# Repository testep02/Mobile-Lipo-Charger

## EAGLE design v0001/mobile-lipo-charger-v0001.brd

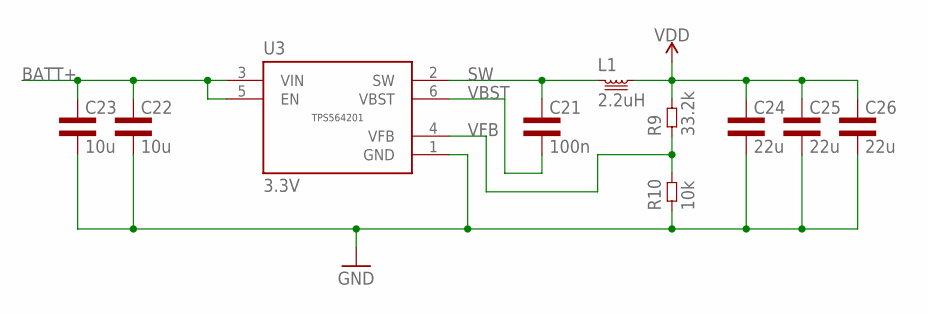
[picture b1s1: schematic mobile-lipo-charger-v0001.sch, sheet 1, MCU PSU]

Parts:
C21: 100n; 0603L3
C22, C23: 10u; 1206L3
C24, C25, C26: 22u; 0603L3
L1: 2.2uH; 6X6; PART-NUM 810-VLS6045EX-2R2N
R9: 33.2k; 0402L3
R10: 10k; 0402L3
U3: 3.3V; SOT-1.1

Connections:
BATT+: C22.1, C23.1, U3.3 (VIN), U3.5 (EN); also elsewhere on the board
GND: C22.2, C23.2, C24.P$2 (2), C25.P$2 (2), C26.P$2 (2), R10.P$1 (1), U3.1 (GND); also elsewhere on the board
SW: C21.P$1 (1), L1.1, U3.2 (SW)
VBST: C21.P$2 (2), U3.6 (VBST)
VDD: C24.P$1 (1), C25.P$1 (1), C26.P$1 (1), L1.2, R9.P$2 (2); also elsewhere on the board
VFB: R9.P$1 (1), R10.P$2 (2), U3.4 (VFB)

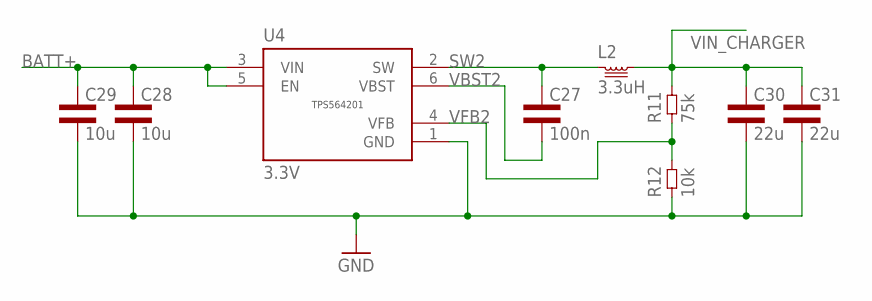
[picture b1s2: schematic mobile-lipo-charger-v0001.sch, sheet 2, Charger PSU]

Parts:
C27: 100n; 0603L3
C28, C29: 10u; 1206L3
C30, C31: 22u; 0603L3
L2: 3.3uH; 6X6; PART-NUM 810-VLS6045EX-3R3N
R11: 75k; 0402L3
R12: 10k; 0402L3
U4: 3.3V; SOT-1.1

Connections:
BATT+: C28.1, C29.1, U4.3 (VIN), U4.5 (EN); also elsewhere on the board
GND: C28.2, C29.2, C30.P$2 (2), C31.P$2 (2), R12.P$1 (1), U4.1 (GND); also elsewhere on the board
SW2: C27.P$1 (1), L2.1, U4.2 (SW)
VBST2: C27.P$2 (2), U4.6 (VBST)
VFB2: R11.P$1 (1), R12.P$2 (2), U4.4 (VFB)
VIN_CHARGER: C30.P$1 (1), C31.P$1 (1), L2.2, R11.P$2 (2); also elsewhere on the board

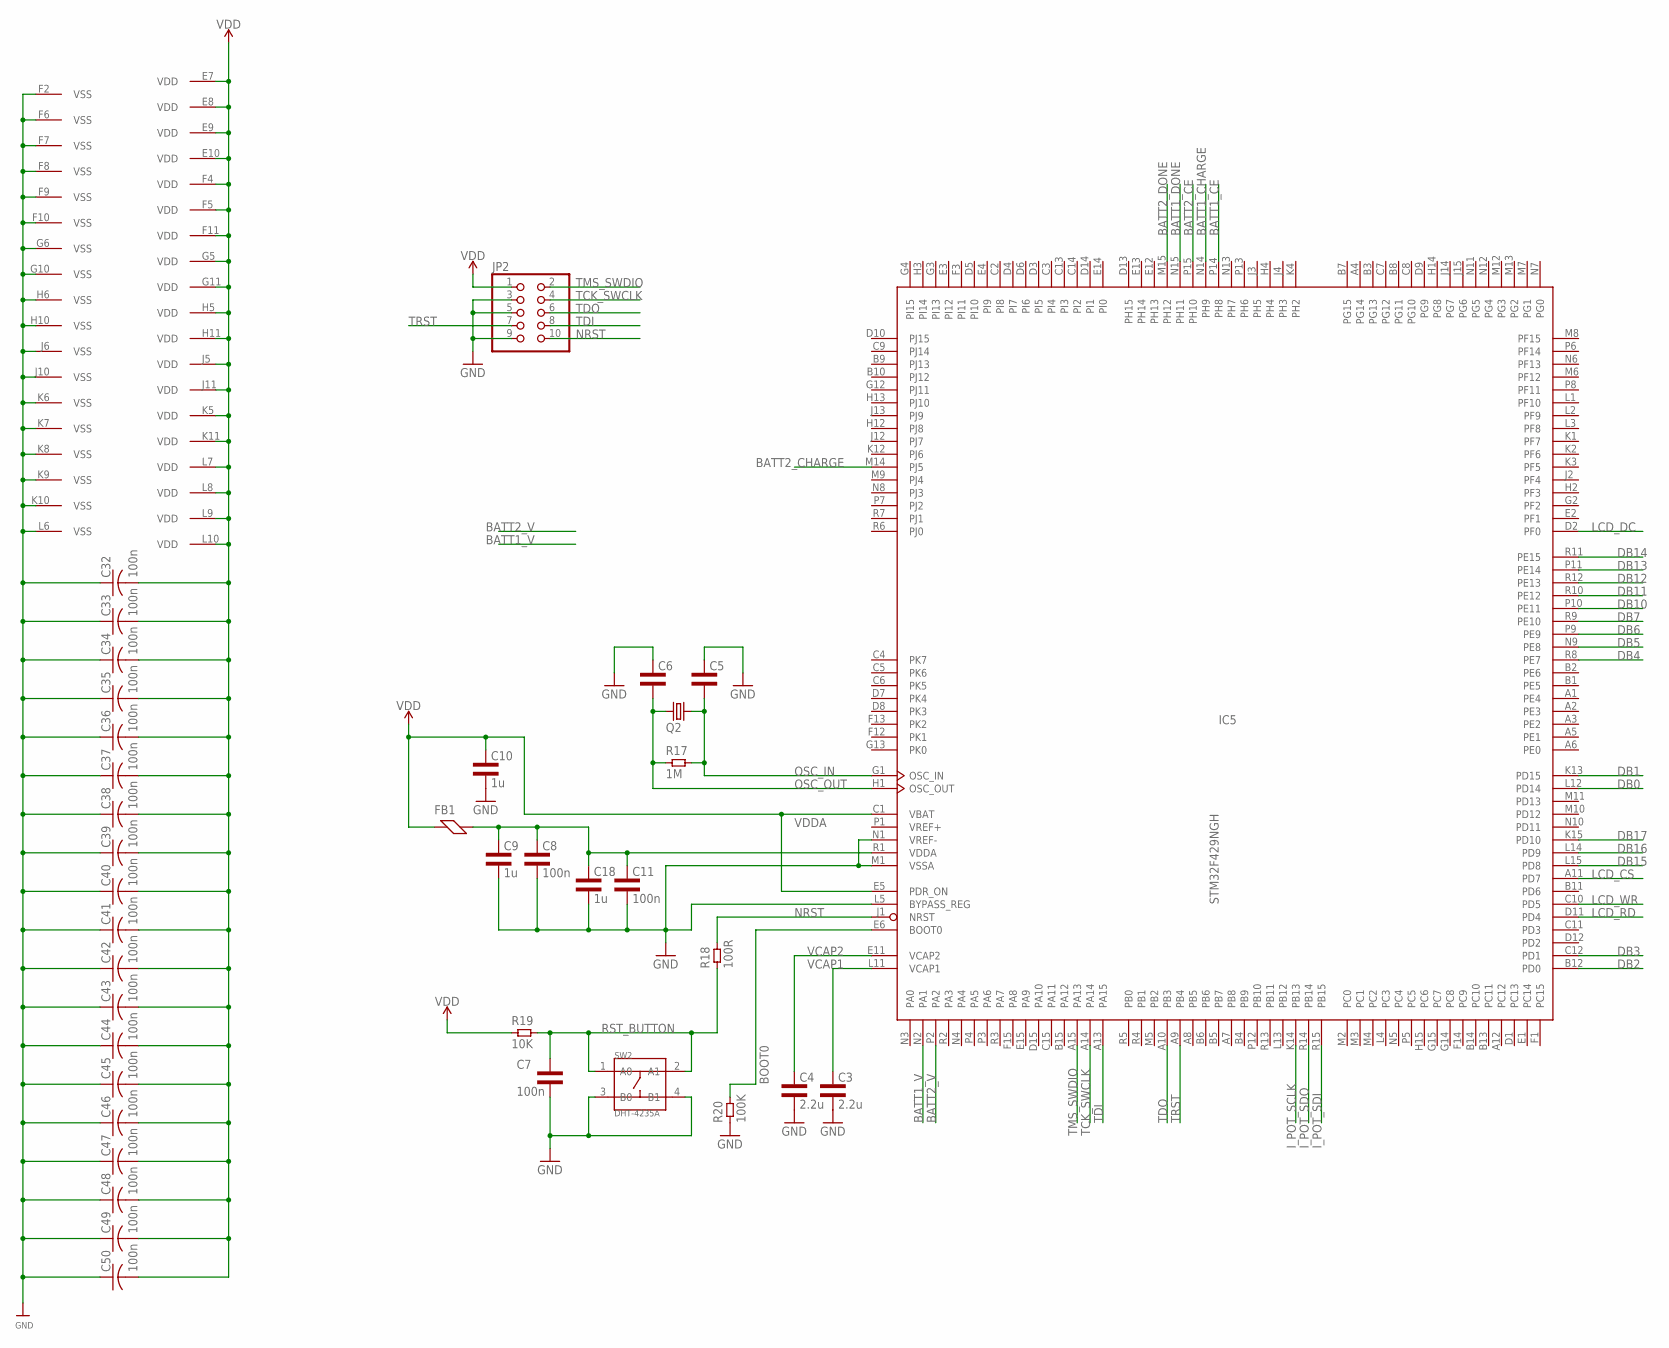
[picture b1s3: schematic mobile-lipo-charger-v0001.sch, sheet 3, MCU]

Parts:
C3, C4: 2.2u; 0805L3; PART-NUM 581-TAJR225K016RNJ
C5, C6: CAP0603L3; 0603L3
C7, C8, C11: 100n; 0402L3
C9, C18: 1u; 0805L3
C10: 1u; 0603L3
C32, C33, C34, C35, C36, C37, C38, C39, C40, C41, C42, C43, C44, C45, C46, C47, C48, C49, C50: 100n; C0201
FB1: FERRITE0603L3; 0603L3
IC5: STM32F429NGH; TFBGA216
JP2: PINHD-2X5; 2X05
Q2: CRYSTALHC49US; PCM2707_V1_SPARKFUN_HC49US
R17: 1M; 0603L3
R18: 100R; 0603L3
R19: 10K; 0603L3
R20: 100K; 0603L3
SW2: DHT-4235A; SW4-SMD-4.2X3.2X2.5MM

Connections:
BATT1_CE: IC5.P14 (PH8); also elsewhere on the board
BATT1_CHARGE: IC5.N14 (PH9); also elsewhere on the board
BATT1_DONE: IC5.N15 (PH11); also elsewhere on the board
BATT1_V: IC5.N2 (PA1); also elsewhere on the board
BATT2_CE: IC5.P15 (PH10); also elsewhere on the board
BATT2_CHARGE: IC5.M14 (PJ5); also elsewhere on the board
BATT2_DONE: IC5.M15 (PH12); also elsewhere on the board
BATT2_V: IC5.P2 (PA2); also elsewhere on the board
BOOT0: IC5.E6 (BOOT0), R20.P$2 (2)
DB0: IC5.L12 (PD14); also elsewhere on the board
DB1: IC5.K13 (PD15); also elsewhere on the board
DB2: IC5.B12 (PD0); also elsewhere on the board
DB3: IC5.C12 (PD1); also elsewhere on the board
DB4: IC5.R8 (PE7); also elsewhere on the board
DB5: IC5.N9 (PE8); also elsewhere on the board
DB6: IC5.P9 (PE9); also elsewhere on the board
DB7: IC5.R9 (PE10); also elsewhere on the board
DB10: IC5.P10 (PE11); also elsewhere on the board
DB11: IC5.R10 (PE12); also elsewhere on the board
DB12: IC5.R12 (PE13); also elsewhere on the board
DB13: IC5.P11 (PE14); also elsewhere on the board
DB14: IC5.R11 (PE15); also elsewhere on the board
DB15: IC5.L15 (PD8); also elsewhere on the board
DB16: IC5.L14 (PD9); also elsewhere on the board
DB17: IC5.K15 (PD10); also elsewhere on the board
GND: C3.2, C4.2, C5.P$1 (1), C6.P$1 (1), C7.P$2 (2), C8.P$2 (2), C9.2, C10.P$2 (2), C11.P$2 (2), C18.2, C32.1, C33.1, C34.1, C35.1, C36.1, C37.1, C38.1, C39.1, C40.1, C41.1, C42.1, C43.1, C44.1, C45.1, C46.1, C47.1, C48.1, C49.1, C50.1, IC5.F2 (VSS), IC5.F6 (VSS), IC5.F7 (VSS), IC5.F8 (VSS), IC5.F9 (VSS), IC5.F10 (VSS), IC5.G6 (VSS), IC5.G10 (VSS), IC5.H6 (VSS), IC5.H10 (VSS), IC5.J6 (VSS), IC5.J10 (VSS), IC5.K6 (VSS), IC5.K7 (VSS), IC5.K8 (VSS), IC5.K9 (VSS), IC5.K10 (VSS), IC5.L5 (BYPASS_REG), IC5.L6 (VSS), IC5.M1 (VSSA), IC5.N1 (VREF-), JP2.3, JP2.5, JP2.9, R20.P$1 (1), SW2.3 (B0), SW2.4 (B1); also elsewhere on the board
I_POT_SCLK: IC5.K14 (PB13); also elsewhere on the board
I_POT_SDI: IC5.R15 (PB15); also elsewhere on the board
I_POT_SDO: IC5.R14 (PB14); also elsewhere on the board
LCD_CS: IC5.A11 (PD7); also elsewhere on the board
LCD_DC: IC5.D2 (PF0); also elsewhere on the board
LCD_RD: IC5.D11 (PD4); also elsewhere on the board
LCD_WR: IC5.C10 (PD5); also elsewhere on the board
NRST: IC5.J1 (NRST), JP2.10, R18.P$2 (2)
OSC_IN: C5.P$2 (2), IC5.G1 (OSC_IN), Q2.2, R17.P$2 (2)
OSC_OUT: C6.P$2 (2), IC5.H1 (OSC_OUT), Q2.1, R17.P$1 (1)
RST_BUTTON: C7.P$1 (1), R18.P$1 (1), R19.P$2 (2), SW2.1 (A0), SW2.2 (A1)
TCK_SWCLK: IC5.A14, JP2.4
TDI: IC5.A13 (PA15), JP2.8
TDO: IC5.A10 (PB3), JP2.6
TMS_SWDIO: IC5.A15 (PA13), JP2.2
TRST: IC5.A9 (PB4), JP2.7
VCAP1: C3.1, IC5.L11 (VCAP1)
VCAP2: C4.1, IC5.E11 (VCAP2)
VDD: C10.P$1 (1), C32.2, C33.2, C34.2, C35.2, C36.2, C37.2, C38.2, C39.2, C40.2, C41.2, C42.2, C43.2, C44.2, C45.2, C46.2, C47.2, C48.2, C49.2, C50.2, FB1.P$1 (1), IC5.C1 (VBAT), IC5.E5 (PDR_ON), IC5.E7 (VDD), IC5.E8 (VDD), IC5.E9 (VDD), IC5.E10 (VDD), IC5.F4 (VDD), IC5.F5 (VDD), IC5.F11 (VDD), IC5.G5 (VDD), IC5.G11 (VDD), IC5.H5 (VDD), IC5.H11 (VDD), IC5.J5 (VDD), IC5.J11 (VDD), IC5.K5 (VDD), IC5.K11 (VDD), IC5.L7 (VDD), IC5.L8 (VDD), IC5.L9 (VDD), IC5.L10 (VDD), JP2.1, R19.P$1 (1); also elsewhere on the board
VDDA: C8.P$1 (1), C9.1, C11.P$1 (1), C18.1, FB1.P$2 (2), IC5.R1 (VDDA)
VREF+: IC5.P1 (VREF+)

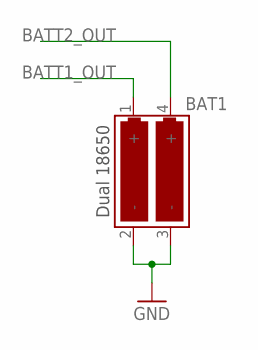
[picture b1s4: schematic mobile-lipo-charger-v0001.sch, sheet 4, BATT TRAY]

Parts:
BAT1: KEYSTONE1048

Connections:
BATT1_OUT: BAT1.1 (+); also elsewhere on the board
BATT2_OUT: BAT1.4 (+); also elsewhere on the board
GND: BAT1.2 (-), BAT1.3 (-); also elsewhere on the board

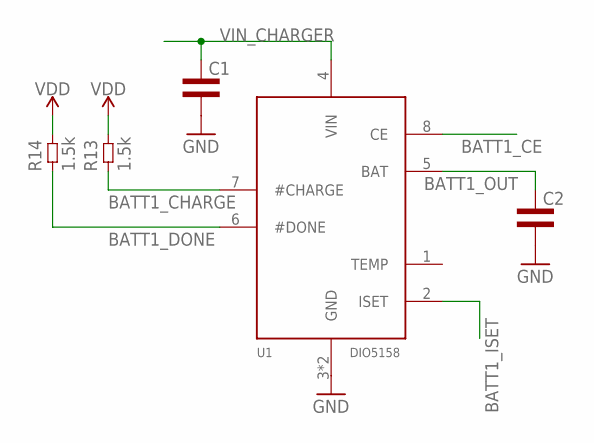
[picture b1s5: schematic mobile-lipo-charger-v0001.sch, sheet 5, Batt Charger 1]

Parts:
C1, C2: CAP0805L3; 0805L3
R13, R14: 1.5k; 0603L3
U1: DIO5158XS8; EP-MSOP8

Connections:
BATT1_CE: U1.8 (CE); also elsewhere on the board
BATT1_CHARGE: R13.P$1 (1), U1.7 (#CHARGE); also elsewhere on the board
BATT1_DONE: R14.P$1 (1), U1.6 (#DONE); also elsewhere on the board
BATT1_ISET: U1.2 (ISET); also elsewhere on the board
BATT1_OUT: C2.1, U1.5 (BAT); also elsewhere on the board
GND: C1.2, C2.2, U1.3 (GND), U1.TP (GND); also elsewhere on the board
VDD: R13.P$2 (2), R14.P$2 (2); also elsewhere on the board
VIN_CHARGER: C1.1, U1.4 (VIN); also elsewhere on the board

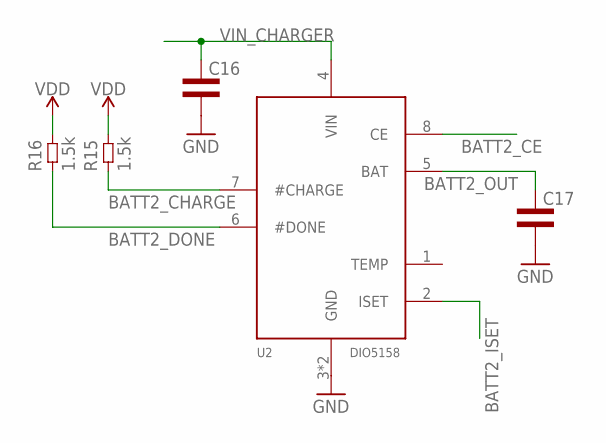
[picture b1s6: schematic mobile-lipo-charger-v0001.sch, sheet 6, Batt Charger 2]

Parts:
C16, C17: CAP0805L3; 0805L3
R15, R16: 1.5k; 0603L3
U2: DIO5158XS8; EP-MSOP8

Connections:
BATT2_CE: U2.8 (CE); also elsewhere on the board
BATT2_CHARGE: R15.P$1 (1), U2.7 (#CHARGE); also elsewhere on the board
BATT2_DONE: R16.P$1 (1), U2.6 (#DONE); also elsewhere on the board
BATT2_ISET: U2.2 (ISET); also elsewhere on the board
BATT2_OUT: C17.1, U2.5 (BAT); also elsewhere on the board
GND: C16.2, C17.2, U2.3 (GND), U2.TP (GND); also elsewhere on the board
VDD: R15.P$2 (2), R16.P$2 (2); also elsewhere on the board
VIN_CHARGER: C16.1, U2.4 (VIN); also elsewhere on the board

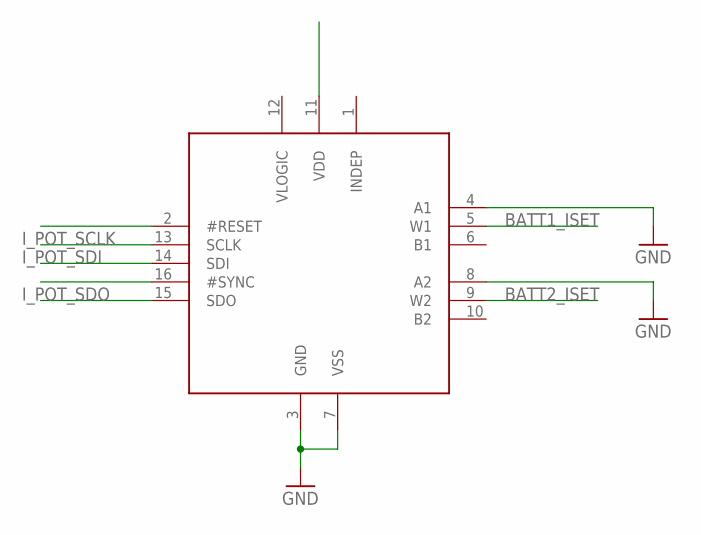
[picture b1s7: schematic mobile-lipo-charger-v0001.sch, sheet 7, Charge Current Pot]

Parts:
U$1: AD5122BRUZ10; TSSOP-RU-16; PART-NUM 584-AD5122BRUZ10

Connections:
BATT1_ISET: U$1.5 (W1); also elsewhere on the board
BATT2_ISET: U$1.9 (W2); also elsewhere on the board
GND: U$1.3 (GND), U$1.4 (A1), U$1.7 (VSS), U$1.8 (A2); also elsewhere on the board
I_POT_SCLK: U$1.13 (SCLK); also elsewhere on the board
I_POT_SDI: U$1.14 (SDI); also elsewhere on the board
I_POT_SDO: U$1.15 (SDO); also elsewhere on the board

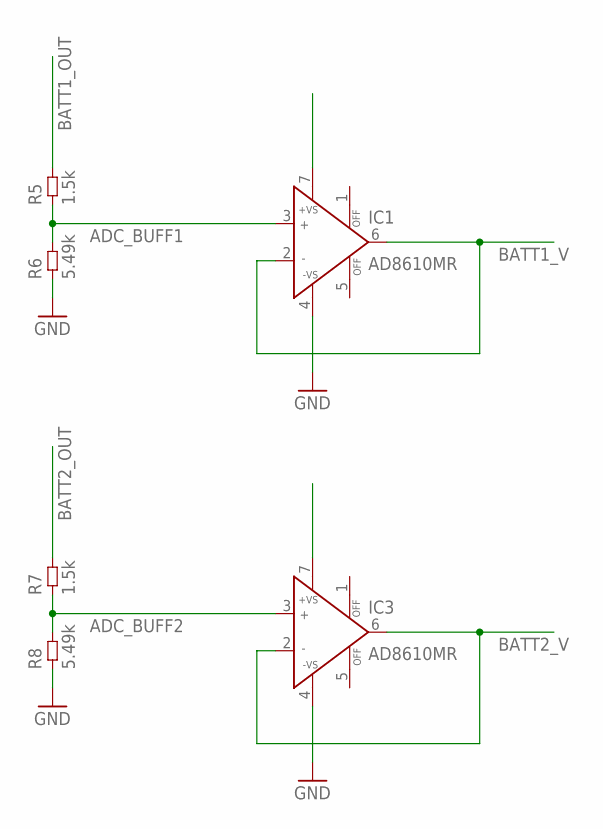
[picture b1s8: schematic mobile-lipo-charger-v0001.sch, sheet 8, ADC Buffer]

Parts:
IC1, IC3: AD8610MR; MSOP08
R5, R7: 1.5k; 0603L3
R6, R8: 5.49k; 0603L3

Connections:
ADC_BUFF1: IC1.3 (IN+), R5.P$1 (1), R6.P$2 (2)
ADC_BUFF2: IC3.3 (IN+), R7.P$1 (1), R8.P$2 (2)
BATT1_OUT: R5.P$2 (2); also elsewhere on the board
BATT1_V: IC1.2 (IN-), IC1.6 (OUT); also elsewhere on the board
BATT2_OUT: R7.P$2 (2); also elsewhere on the board
BATT2_V: IC3.2 (IN-), IC3.6 (OUT); also elsewhere on the board
GND: IC1.4 (-VS), IC3.4 (-VS), R6.P$1 (1), R8.P$1 (1); also elsewhere on the board

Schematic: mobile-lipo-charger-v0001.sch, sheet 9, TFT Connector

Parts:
J1: 68715014022
R1: 1k; 0603L3
R2: 10k; 0603L3
R3: 12R; 0603L3
T1, T2, T3: BC846; SOT23

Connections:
DB0: J1.32; also elsewhere on the board
DB1: J1.31; also elsewhere on the board
DB2: J1.30; also elsewhere on the board
DB3: J1.29; also elsewhere on the board
DB4: J1.28; also elsewhere on the board
DB5: J1.27; also elsewhere on the board
DB6: J1.26; also elsewhere on the board
DB7: J1.25; also elsewhere on the board
DB10: J1.22; also elsewhere on the board
DB11: J1.21; also elsewhere on the board
DB12: J1.20; also elsewhere on the board
DB13: J1.19; also elsewhere on the board
DB14: J1.18; also elsewhere on the board
DB15: J1.17; also elsewhere on the board
DB16: J1.16; also elsewhere on the board
DB17: J1.15; also elsewhere on the board
ENABLE: J1.14
GND: J1.6, J1.7, J1.8, J1.11, J1.12, J1.13, J1.23, J1.24, J1.34, J1.43, J1.48, J1.49, J1.50, R3.P$1 (1), T3.2 (E); also elsewhere on the board
LCD_BLED: R1.P$1 (1)
LCD_CS: J1.38; also elsewhere on the board
LCD_DC: J1.37; also elsewhere on the board
LCD_RD: J1.35; also elsewhere on the board
LCD_WR: J1.36; also elsewhere on the board
unnamed: T2.2 (E), T3.1 (B), T3.3 (C)
unnamed: R3.P$2 (2), T1.2 (E)
unnamed: R1.P$2 (2), R2.P$1 (1), T1.1 (B), T2.1 (B), T2.3 (C)
RST: J1.10
TFT_LED_K: J1.1, T1.3 (C)
TFT_XL: J1.46
TFT_XR: J1.44
TFT_YD: J1.45
TFT_YU: J1.47
VCC_BLED: J1.2, J1.3, J1.4, J1.5
VDD: J1.9, J1.40, J1.41, J1.42, R2.P$2 (2); also elsewhere on the board

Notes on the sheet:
LEDK
LEDA1
LEDA2
LEDA3
LEDA4
IM0
IM1
IM2
IM3
RESET
VSYNC
HSYNC
DOTCLK
DB17
DB16
DB15
DB14
DB13
DB12
DB11
DB10
DB9
DB8
DB7
DB6
DB5
DB4
DB3
DB2
DB1
DB0
SDO
SDI
WRX(D/CX)
D/CX(SCL
CSX
VDDI
VCI
GND

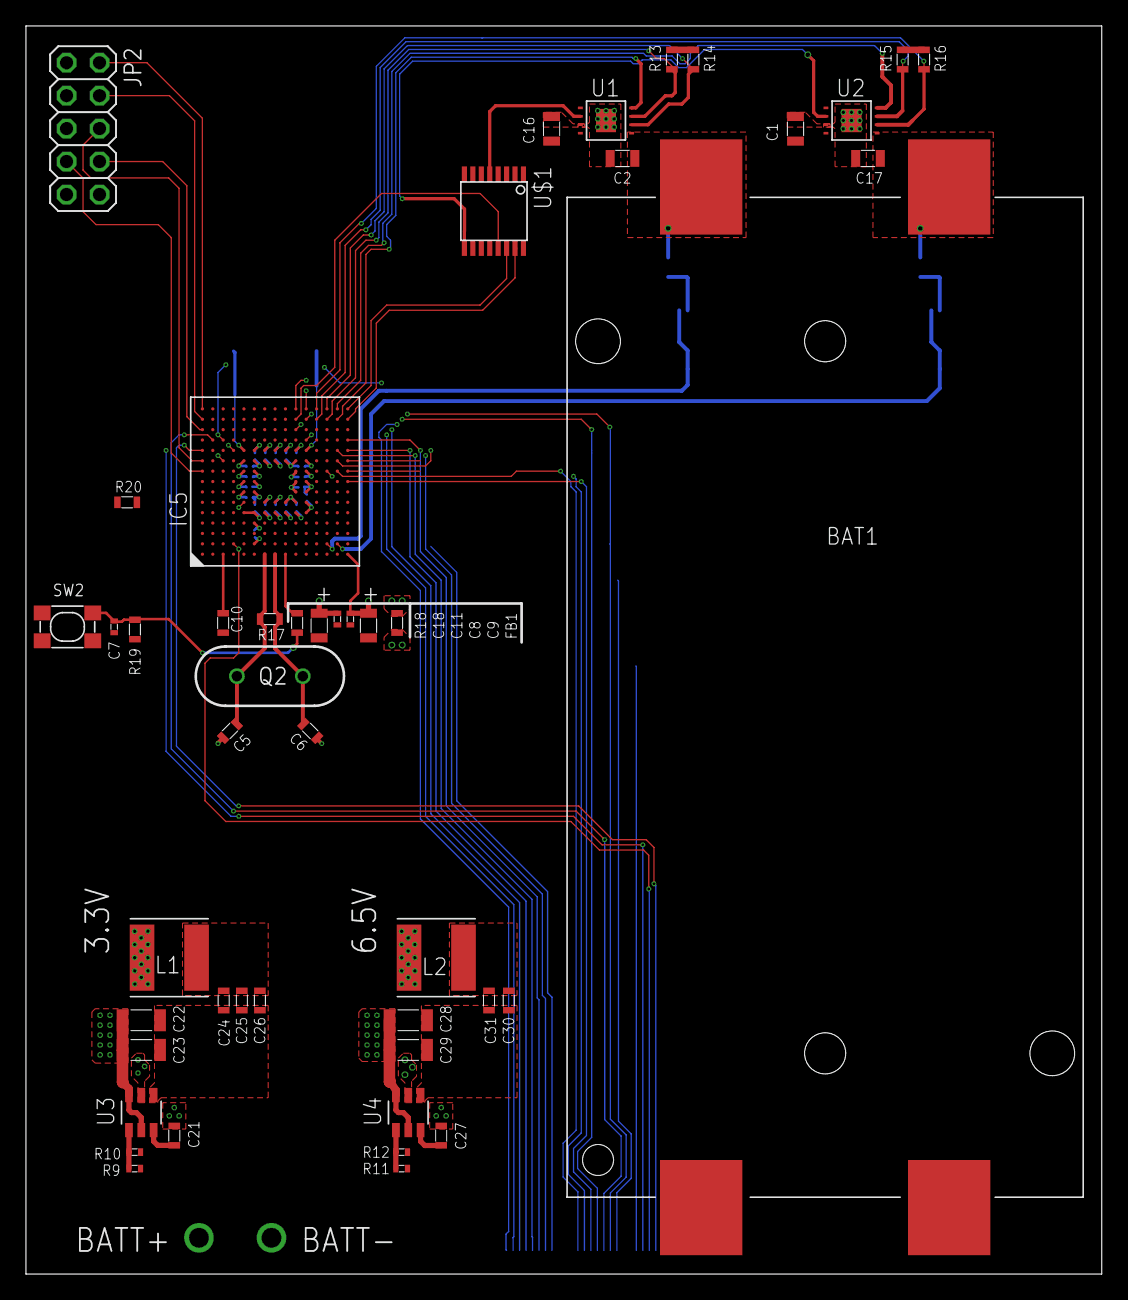
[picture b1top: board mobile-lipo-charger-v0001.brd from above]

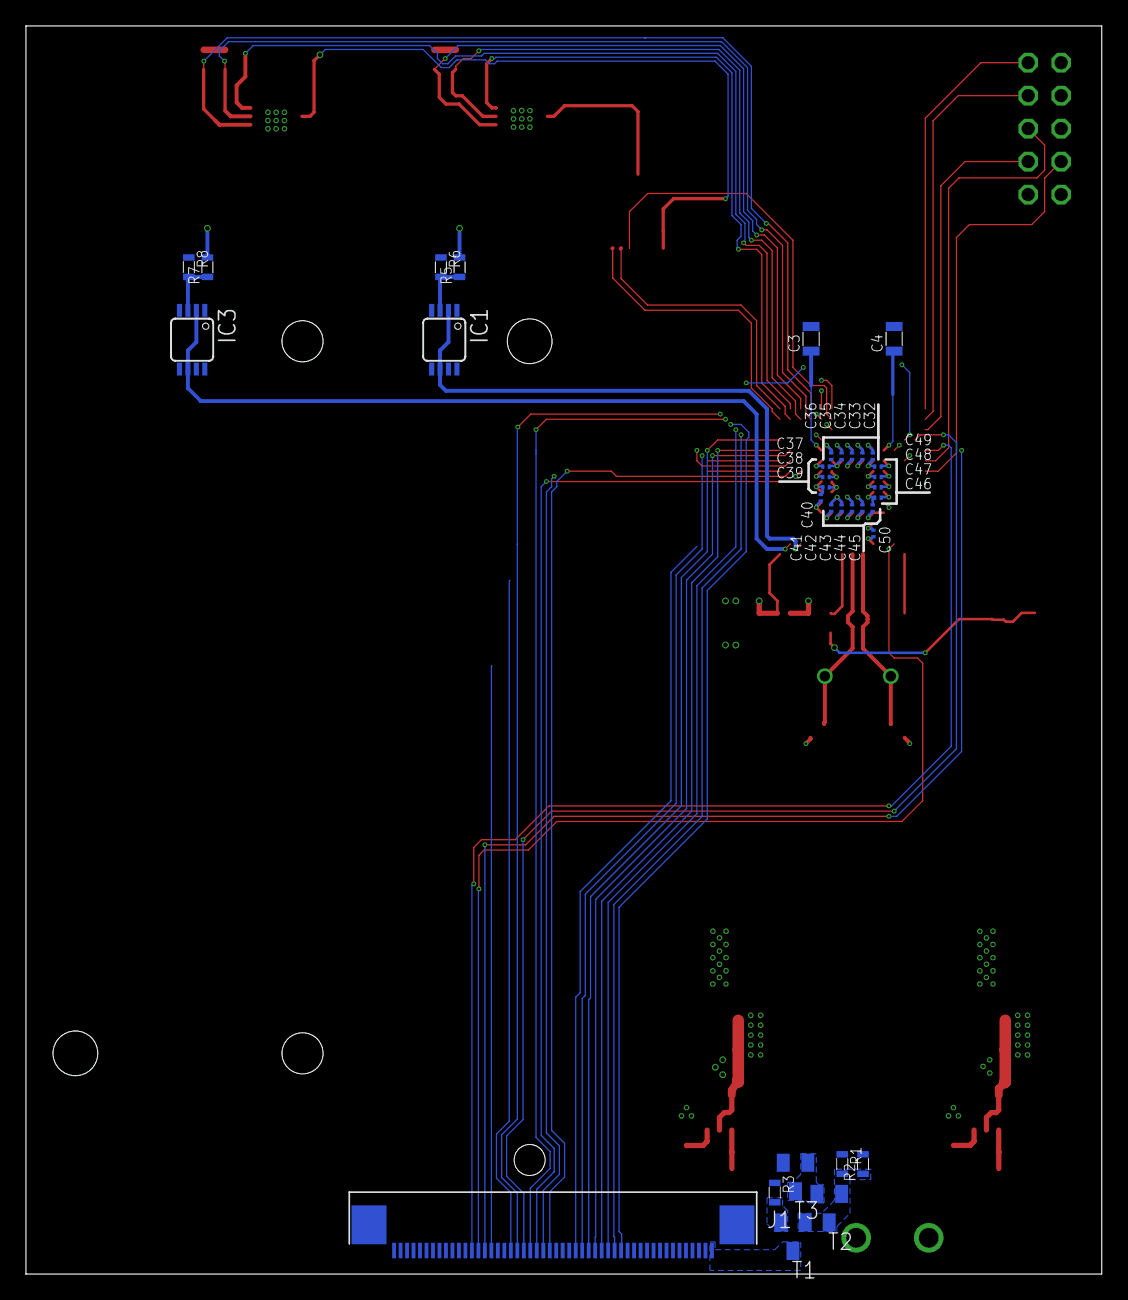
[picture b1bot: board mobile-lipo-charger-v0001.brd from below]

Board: 4 copper layers, 82.9 x 96.2 mm, 82 parts (34 on the bottom side), 65 nets.

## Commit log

2020-01-29 Initial commit
    Initial commit
2020-01-29 Minor Changes
    Made minor changes to the polygons for the charger chips
2020-01-29 Added ADC Buffer
    Added the ADC buffer and voltage divider for measuring the battery voltage before/during/after charging
2020-01-30 Added buffers
    Added the buffers to the ADC for the MCU and laid out the board for those parts.
2020-01-30 Charger Chip Enable
    Routed the charger chip enable lines.
2020-01-30 Added 3.3V rail
    Added the 3.3V rail switching supply
2020-01-30 Reroute
    Rerouted some traces to the bottom layer
2020-01-30 Added new routes
    Added routes form CHARGE and DONE lines of both charger chips.
2020-01-31 Changed PSU Inductors
    Changed the inductors for the PSUs to be smaller footprint.
2020-02-01 Added Pullups
    Added pull-up resistors to the charger chips.
2020-02-01 Minor change
    Minor change
2020-02-01 blah
    blah
2020-02-02 Once again, removing temp files
    Removed the .b# and .s# files that are clutter from the repo....again
2020-02-04 Major Changes
    Changed the STM32F401 to an STM32F429 BGA chip and began routing the board around those changes.
2020-02-05 Routed
    Routed new chip
2020-02-05 Routed ferrite bead
    Routed the ferrite bead for VDDA and VREF+
2020-02-06 Routing
    Began routing TFT signals
2020-02-07 Routing
    Routed some signals for the TFT
2020-02-08 LED Backlight
    Added the LCD backlight control and PSU
2020-02-09 TFT Changes
    Changed the data lines to the TFT and rerouted some of the charge IC lines
2020-02-10 TFT Routing
    Began routing the TFT connections from the MCU BGA to the FPC

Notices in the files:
parts and their libraries:
Wurth_Elektronik_Electromechanic_FPC_Con: Copyright: Würth Elektronik
SparkFun-PowerSymbols: Licensing: Creative Commons ShareAlike 4.0 International - https://creativecommons.org/licenses/by-sa/4.0
